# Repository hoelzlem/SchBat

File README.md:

# SchBat
Schaltungsentwicklung für Batteriesysteme Praktikum

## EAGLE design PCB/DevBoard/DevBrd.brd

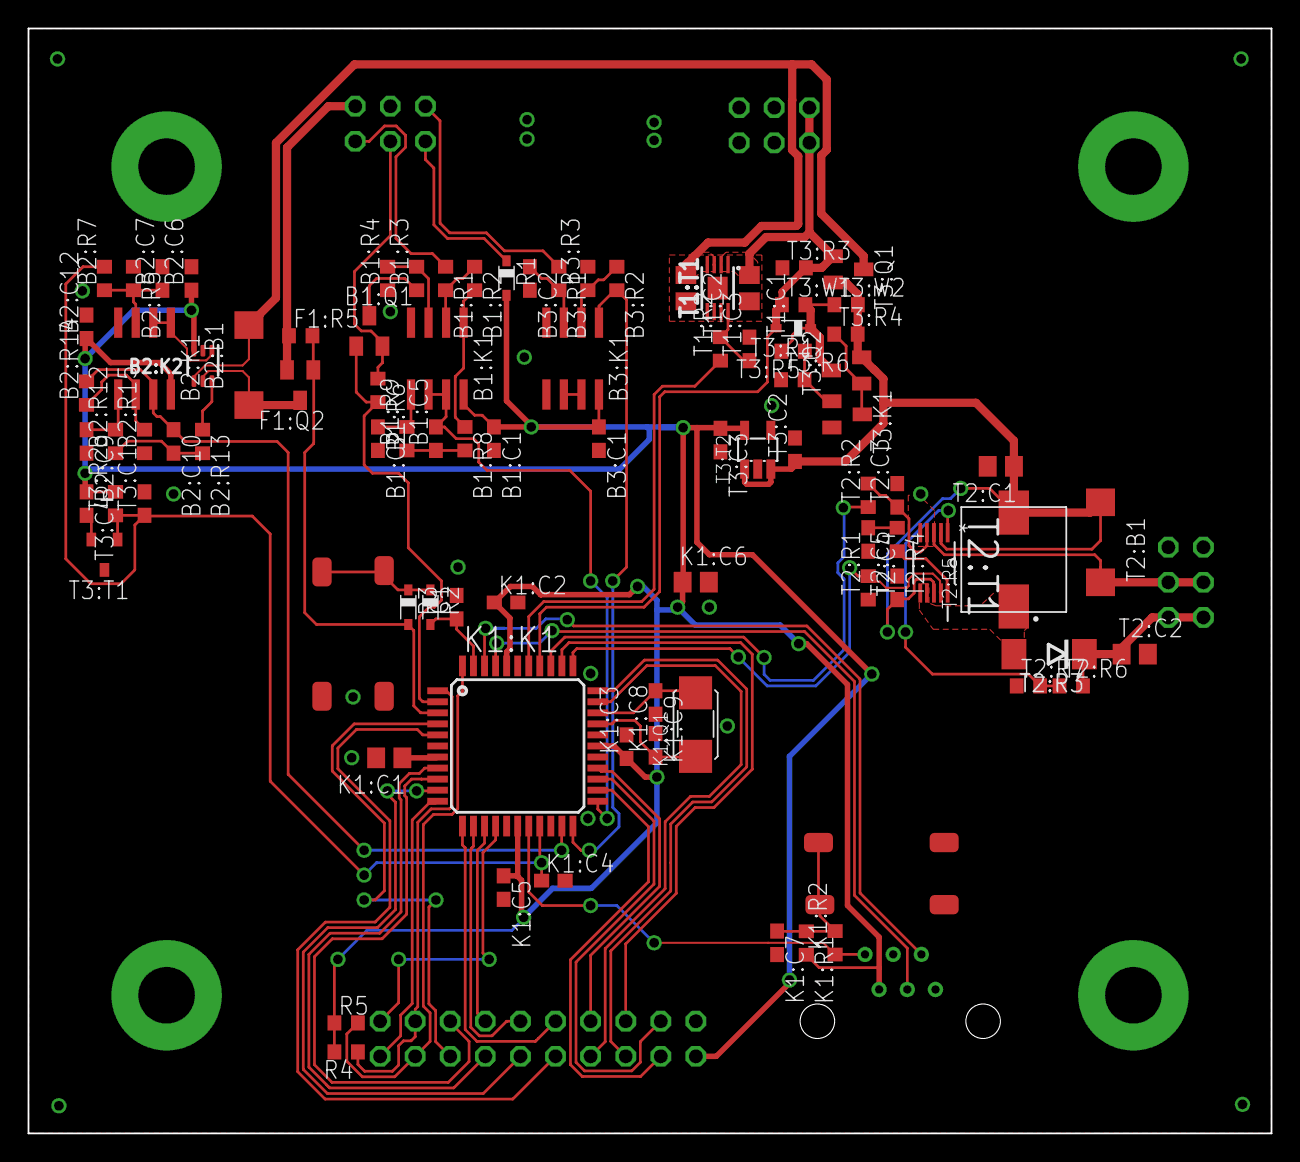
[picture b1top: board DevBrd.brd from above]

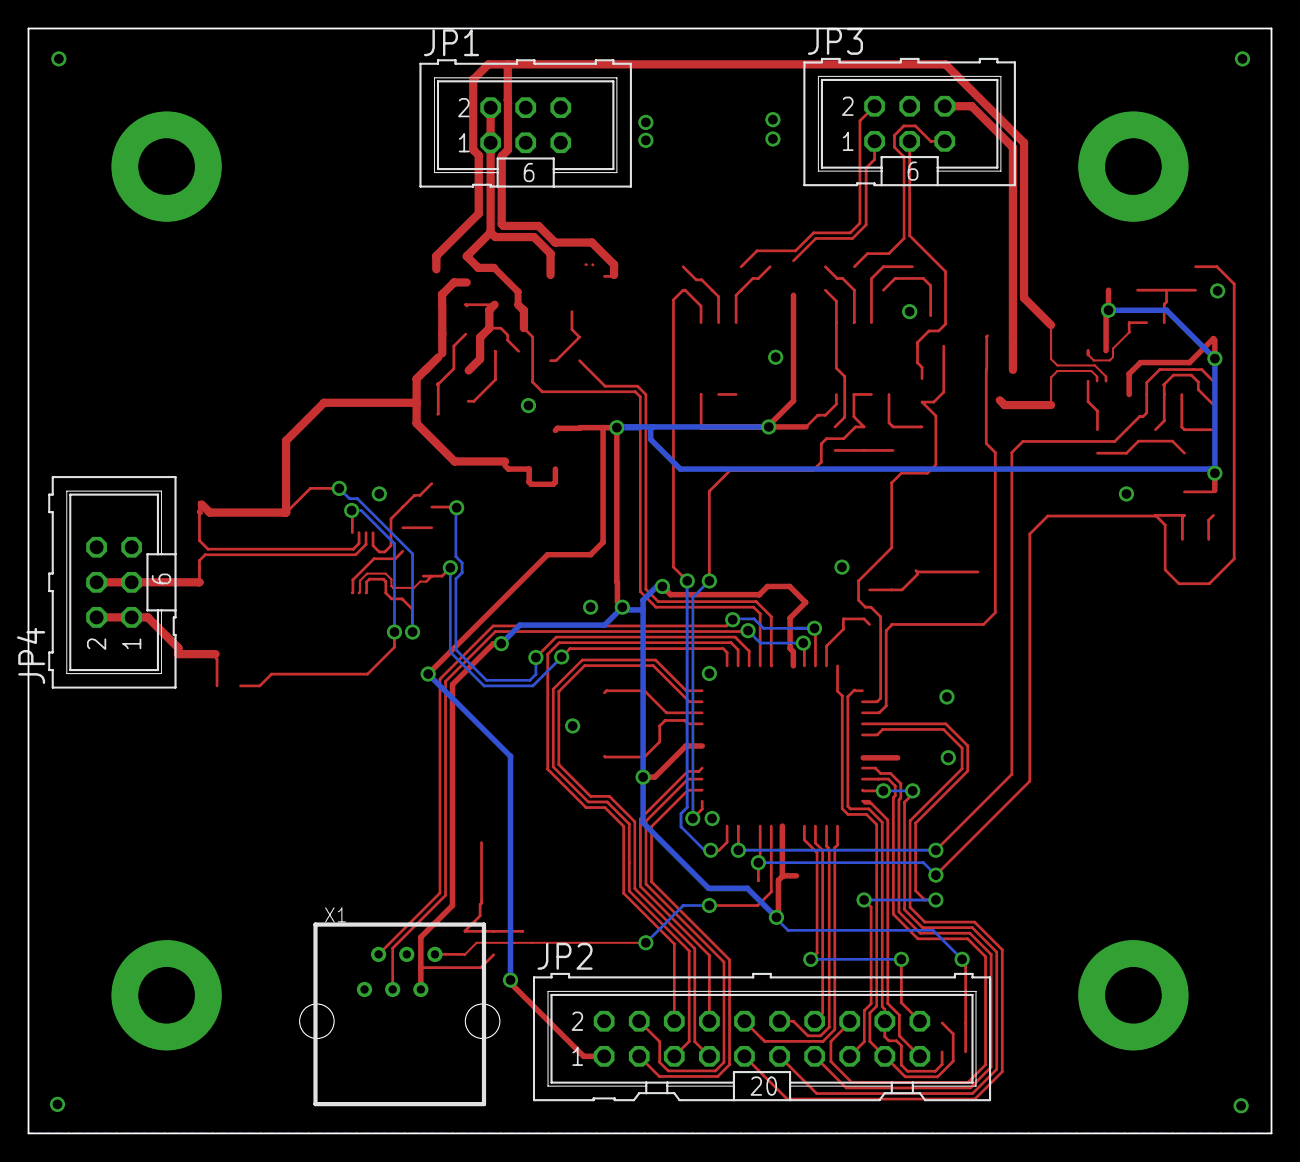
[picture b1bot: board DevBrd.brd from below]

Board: 2 copper layers, 90.0 x 80.0 mm, 96 parts (5 on the bottom side), 73 nets.

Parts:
B1:C1, B2:C6, B2:C12, B3:C1: 100 n / 6.3 V; C0603
B1:C2, B2:C9: 1.5 n / 6.3 V; C0603
B1:C5, B2:C10: 15 n / 6.3 V; C0603
B1:K1, B2:K1, B3:K1: MCP662; SO-8
B1:Q1: RZR040P01TL; SOT-23-3
B1:R1, B1:R3: 17.4 k; R0603
B1:R2, B1:R4, B1:R6: 10 k; R0603
B1:R8: 7.5 k; R0603
B1:R9: 133 k; R0603
B2:B1: 5 m; R2512W
B2:C7: 1 µ / 6.3 V; C0603
B2:K2: INA210; SC70-6
B2:R5: 2.94 k; R0603
B2:R7: 9.31 k; R0603
B2:R12: 143 k; R0603
B2:R13: 6.81 k; R0603
B2:R14: 3.92 k; R0603
B2:R15: 28 k; R0603
B3:C2: 150 n / 6.3 V; C0603
B3:R1: 100 k; R0603
B3:R2: 56.2 k; R0603
B3:R3: 44.2 k; R0603
C1: 100 n / 6.3 V; C0603
F1:Q2: RZR040P01TL; SOT-23-3
F1:R5: 10 k; R0603
JP1, JP3, JP4: 2.54 mm male; ML6
JP2: 2.54 mm male; ML20
K1:C1: 10 µ / 6.3 V; C0805
K1:C2, K1:C3, K1:C4, K1:C5, K1:C7: 100 n / 6.3 V; C0603
K1:C6: 4.7 µ / 6.3 V; C0805
K1:C8, K1:C9: 18 p / 6.3 V; C0603
K1:K1: PIC32MX150F128D; TQFP-44
K1:Q1: ABM3
K1:R1: 10 k; R0603
K1:R2: 1 k; R0603
K1:S1: JTP1138X6
R1, R2, R3: BAT60; SOD323
R4, R5: 4.7 k; R0603
S1: JTP1138X6
T1:C1, T1:C2, T2:C1: 4.7 µ / 10 V; C0805
T1:C3, T2:C3, T3:C1, T3:C3, T3:C4: 1 µ / 6.3 V; C0603
T1:R2, T3:R4: 2 k; R0603
T1:T1: MCP73831DFN; MCP73831_DFN
T2:B1: 50 m; R2512W
T2:C2: 4.7 µ / 25 V; C0805
T2:C4, T2:C5: 10 n / 6.3 V; C0603
T2:R1, T3:R3: 10 k; R0603
T2:R2: 1 k; R0603
T2:R3: STPS1L30U; DO214AA
T2:R4, T3:W1, T3:W2: 0; R0603
T2:R5: MCSDRH73B
T2:R6: 102 k; R0603
T2:R7: 14.7 k; R0603
T2:T1: LT1618EMSPBF; SOP50P490X110-10N
T3:C2: 1 µ / 10 V; C0603
T3:K1: IRLML6344TRPBF; SOT-23-3
T3:Q1, T3:Q2: RZR040P01TL; SOT-23-3
T3:R1: BAT60; SOD323
T3:R2: 300; R0603
T3:R5: 3.64 k; R0603
T3:R6: 1.3 k; R0603
T3:T1: LM4040A25IDBZT; DBZ_R-PDSO-G3
T3:T2: XC6210B332MR; SOT-23-5L
X1: RJ11WüRTH; XRJK-S-01-6-6-0-2G2-NO

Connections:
!BAT_CONNECT: F1:Q2.1, F1:R5.2, K1:K1.3, R3.A
!CH_CTRL: K1:K1.38, T1:R2.1
!LED_SHDN: K1:K1.34, T2:R1.2, T2:T1.9
!MCLR: K1:K1.18, K1:R2.1, X1.6
!U_SENS_EN: B1:Q1.1, B1:R6.2, K1:K1.2
+2V5: B2:R7.2, K1:C4.1, K1:K1.19, T3:C1.1, T3:R2.1, T3:T1.1
+2V8..3V3: B1:C1.1, B1:K1.8, B2:C6.1, B2:C12.1, B2:K1.8, B2:K2.3, B3:C1.1, B3:K1.8, JP2.1, K1:C2.1, K1:C3.1, K1:C5.1, K1:C6.1, K1:K1.17, K1:K1.28, K1:K1.40, K1:R1.2, R1.A, R4.2, R5.1, T3:C3.1, T3:C4.1, T3:R2.2, T3:T2.5, X1.5
+5V: JP1.1, JP1.2, K1:K1.37, T1:C1.1, T1:T1.1, T1:T1.2, T3:Q1.1, T3:R1.A, T3:R3.2, T3:W1.1
ADC1: JP2.3, K1:K1.24
ADC2: JP2.4, K1:K1.25
B1:N$1: B1:Q1.3, B1:R3.1
B1:N$2: B1:K1.3, B1:R3.2, B1:R4.2
B1:N$3: B1:K1.1, B1:R2.2, B1:R8.1
B1:N$5: B1:K1.2, B1:R1.2, B1:R2.1
B1:N$6: B1:C5.1, B1:R8.2, B1:R9.1
B1:N$9: B1:C2.1, B1:K1.5, B1:R9.2
B2:+0V6: B2:K1.1, B2:K1.2, B2:K2.1
B2:N$1: B2:C7.1, B2:K1.3, B2:R5.2, B2:R7.1
B2:N$4: B2:K2.6, B2:R13.1
B2:N$12: B2:C9.1, B2:K1.5, B2:R12.2
B2:N$13: B2:C10.2, B2:R12.1, B2:R13.2
B2:N$14: B2:K1.6, B2:R14.1, B2:R15.2
B3:N$1: B3:K1.6, B3:K1.7
B3:N$2: B3:C2.1, B3:K1.3, B3:R1.2
B3:N$4: B3:K1.2, B3:R2.1, B3:R3.1
GND: B1:C1.2, B1:C2.2, B1:K1.4, B1:R4.1, B2:C6.2, B2:C7.2, B2:C9.2, B2:C12.2, B2:K1.4, B2:K2.2, B2:R5.1, B2:R15.1, B3:C1.2, B3:C2.2, B3:K1.4, B3:K1.5, B3:R3.2, C1.2, JP1.3, JP1.4, JP2.2, JP3.4, K1:C1.2, K1:C2.2, K1:C3.2, K1:C4.2, K1:C5.2, K1:C6.2, K1:C7.2, K1:C8.2, K1:C9.2, K1:K1.6, K1:K1.16, K1:K1.20, K1:K1.29, K1:K1.39, K1:S1.1, K1:S1.2, S1.1, S1.2, T1:C1.2, T1:C2.2, T1:C3.2, T1:T1.6, T1:T1.9, T2:C1.2, T2:C2.2, T2:C3.2, T2:C4.2, T2:C5.2, T2:R1.1, T2:R7.1, T2:T1.5, T3:C1.2, T3:C2.2, T3:C3.2, T3:C4.2, T3:K1.2, T3:R3.1, T3:R6.1, T3:T1.2, T3:T2.2, X1.4
GPIO1: JP2.5, K1:K1.33
GPIO2: JP2.6, K1:K1.35
GPIO3: JP2.7, K1:K1.32
GPIO4: JP2.8, K1:K1.26
GPIO5: JP2.9, K1:K1.5
GPIO6: JP2.10, K1:K1.12
GPIO7: JP2.11, K1:K1.10
GPIO8: JP2.12, K1:K1.13
GPIO9: JP2.13, K1:K1.8
I_BAT_FORCE+: F1:Q2.2, F1:R5.1, JP3.6
K1:N$2: K1:C1.1, K1:K1.7
K1:N$10: K1:C7.1, K1:R1.1, K1:R2.2, K1:S1.3, K1:S1.4
K1:RA2_OSC1: K1:C8.1, K1:K1.30, K1:Q1.P$1
K1:RA3_OSC2: K1:C9.1, K1:K1.31, K1:Q1.P$2
LED_IADJ: K1:K1.36, T2:R2.1
unnamed: B2:B1.1, B2:K2.5, F1:Q2.3
unnamed: B2:B1.2, B2:K2.4, T1:C2.1, T1:T1.3, T1:T1.4, T3:Q1.3
unnamed: C1.1, K1:K1.43, R2.A
unnamed: R2.C, R3.C, S1.3, S1.4
PGC: K1:K1.42, X1.2
PGD: K1:K1.41, X1.3
SCK1: JP2.14, K1:K1.14
SCL1: JP2.17, K1:K1.44, R5.2
SDA1: JP2.18, K1:K1.1, R4.1
SDI1: JP2.16, K1:K1.9
SDO1: JP2.15, K1:K1.4
T1:N$2: T1:C3.1, T1:R2.2, T1:T1.8
T2:N$1: T2:C3.1, T2:R2.2, T2:T1.4
T2:N$2: T2:R4.2, T2:T1.10
T2:N$3: T2:C4.1, T2:R4.1
T2:N$6: T2:R6.1, T2:R7.2, T2:T1.1
T2:SW: T2:R3.A, T2:R5.P$1, T2:T1.6, T2:T1.7
T3:N$1: T3:Q2.3, T3:R1.C, T3:R5.2, T3:W1.2, T3:W2.1
T3:N$2: T3:K1.3, T3:Q2.1, T3:R4.1
T3:N$3: T3:K1.1, T3:R5.1, T3:R6.2
U1RX: JP2.19, K1:K1.11
U1TX: JP2.20, K1:K1.15
U_I_MEAS: B2:C10.1, B2:K1.7, B2:R14.2, K1:K1.21
U_T_MEAS: B3:K1.1, B3:R2.2, K1:K1.22
U_U_MEAS: B1:C5.2, B1:K1.6, B1:K1.7, K1:K1.23
V+: T2:B1.1, T2:C1.1, T2:C5.1, T2:R5.P$2, T2:T1.2, T2:T1.8, T3:C2.1, T3:Q1.2, T3:Q2.2, T3:R4.2, T3:T2.1, T3:T2.3, T3:W2.2
VDD_SENSOR: JP3.1, R1.C
V_BAT_SENSE+: B1:Q1.2, B1:R6.1, JP3.3
V_BAT_SENSE-: B1:R1.1, JP3.5
V_LED+: JP4.1, JP4.2, T2:C2.1, T2:R3.C, T2:R6.2
V_LED-: JP4.3, JP4.4, T2:B1.2, T2:T1.3
V_SENSOR: B3:R1.1, JP3.2

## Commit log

2018-03-18 Initial commit - containing pin config and autogenerated files
2018-03-18 Added merge configuration for MPLAB project files
2018-03-18 * Removed obsolete files * Added mcc initialisation to main
2018-03-18 * Added procedure for converting ADC measurement to voltage * Added main.h for global definitions
2018-03-18 * Added BMS module with function for calculation of battery voltage, current and temperature
2018-03-18 Added skeleton for BMS state machine
2018-03-21 Further configuration changes
2018-03-26 Rewrote from scratch - AD now working (Vref- as lower reference not working)
2018-03-26 Began with development of mapping from OCV to SOC
2018-03-26 Finished calculation of SOC by OCV
2018-03-28 Added mayor features of BMS
2018-03-29 Minor changes
2018-04-06 Moved software to a separate folder in order to be able to put everything into this repository
2018-04-06 Added content from concept repository
2018-04-06 Added experiments regarding cell identification with Simulink
2018-04-06 Added PCB design files
2018-04-06 * Added design files for closing presentation poster * Moved miscellaneous files to a separate folder
2018-04-06 Added reference manual for PIC32 family
